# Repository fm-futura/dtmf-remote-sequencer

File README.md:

# Remote power sequencer

This is a very simple device to power on or off the transmitter from our
studio using DTMF tones.

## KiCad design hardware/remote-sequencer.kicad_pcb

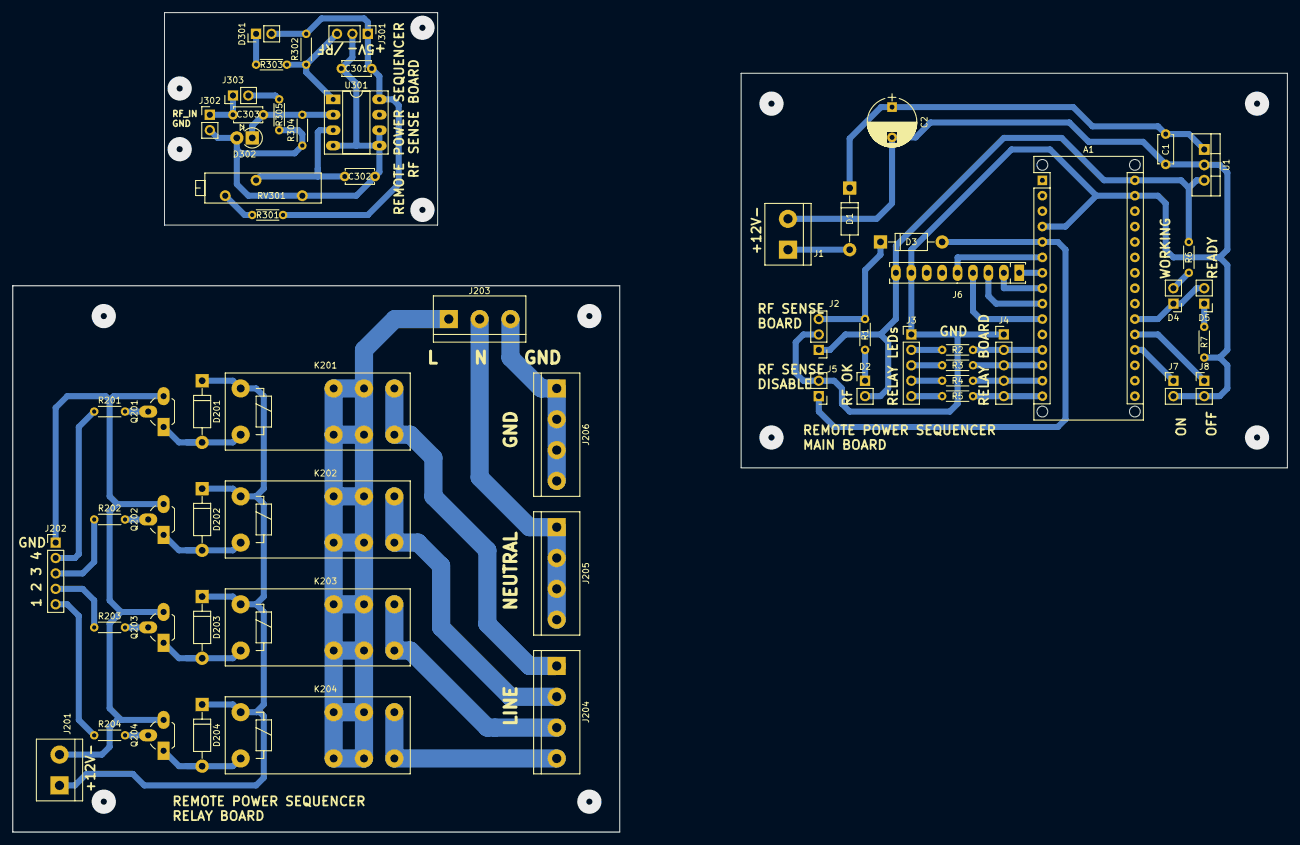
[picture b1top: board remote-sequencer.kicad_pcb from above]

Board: 2 copper layers, 210.0 x 135.0 mm, 61 parts (0 on the bottom side), 51 nets.

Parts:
A1: Arduino_Nano_v3.x; Arduino_Nano_WithMountingHoles
C1, C301, C302, C303: 100n; C_Disc_D4.7mm_W2.5mm_P5.00mm
C2: 2200uF; CP_Radial_D8.0mm_P5.00mm
D1: 1N4007; D_DO-41_SOD81_P10.16mm_Horizontal
D2, D301: RF OK; Socket_Strip_Straight_1x02_Pitch2.54mm
D3, D201, D202, D203, D204: 1N4148; D_DO-41_SOD81_P10.16mm_Horizontal
D4: WORKING; Socket_Strip_Straight_1x02_Pitch2.54mm
D5: READY; Socket_Strip_Straight_1x02_Pitch2.54mm
D302: 1N4148; D_DO-41_SOD81_P2.54mm_Vertical_AnodeUp
J1, J201: PWR_IN; TerminalBlock_bornier-2_P5.08mm
J2, J301: RF_SENSE_BOARD; Pin_Header_Straight_1x03_Pitch2.54mm
J3: RELAY_LED_OUT; Socket_Strip_Straight_1x05_Pitch2.54mm
J4: RELAY_OUT; Socket_Strip_Straight_1x05_Pitch2.54mm
J5: RF_SENSE_DISABLE; Socket_Strip_Straight_1x02_Pitch2.54mm
J6: DTMF_MODULE; SIP9_Housing_BigPads
J7: ON; Socket_Strip_Straight_1x02_Pitch2.54mm
J8: OFF; Socket_Strip_Straight_1x02_Pitch2.54mm
J202: RELAY_IN; Socket_Strip_Straight_1x05_Pitch2.54mm
J203: AC_POWER_IN; TerminalBlock_bornier-3_P5.08mm
J204: PWR_OUT; TerminalBlock_bornier-4_P5.08mm
J205: NEUTRAL_OUT; TerminalBlock_bornier-4_P5.08mm
J206: EARTH_OUT; TerminalBlock_bornier-4_P5.08mm
J302: RF_PROBE_IN; Socket_Strip_Straight_1x02_Pitch2.54mm
J303: 51_ENABLE; Socket_Strip_Straight_1x02_Pitch2.54mm
K201, K202, K203, K204: RELAY_DPDT; Relay_SPDT_Schrack-RP-II-1-16A-FormC_RM5mm
Q201, Q202, Q203, Q204: BC548; TO-92_Rugged
R1, R2, R3, R4, R5, R6, R7, R201, R202, R203, R204, R302, R303: 1k; R_Axial_DIN0204_L3.6mm_D1.6mm_P5.08mm_Horizontal
R301: 10k; R_Axial_DIN0204_L3.6mm_D1.6mm_P5.08mm_Horizontal
R304: 100K; R_Axial_DIN0204_L3.6mm_D1.6mm_P5.08mm_Horizontal
R305: 51; R_Axial_DIN0204_L3.6mm_D1.6mm_P5.08mm_Horizontal
RV301: 1k; Potentiometer_Trimmer_Bourns_3006P
U1: LM7805_TO220; TO-220-3_Vertical
U301: LM393; DIP-8_W7.62mm_Socket_LongPads

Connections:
+5V: A1.30, C301.1, D2.2, D301.2, J2.1, J6.9, J301.1, R6.2, R301.2, R302.2, U1.3, U301.8
+12V: D1.2, D201.1, D202.1, D203.1, D204.1, J1.1, J201.1, K201.A1, K202.A1, K203.A1, K204.A1
/RelayBoard/CTRL_1: J202.2, R201.1
/RelayBoard/CTRL_2: J202.3, R202.1
/RelayBoard/CTRL_3: J202.4, R203.1
/RelayBoard/CTRL_4: J202.5, R204.1
/RelayBoard/PWR_OUT_1: J204.1, K201.14
/RelayBoard/PWR_OUT_2: J204.2, K202.14
/RelayBoard/PWR_OUT_3: J204.3, K203.14
/RelayBoard/PWR_OUT_4: J204.4, K204.14
Earth_Protective: J203.3, J206.1, J206.2, J206.3, J206.4
GND: A1.4, A1.29, C1.2, C2.2, C301.2, C302.2, D302.2, J1.2, J2.2, J3.1, J4.1, J5.2, J6.8, J7.2, J8.2, J201.2, J202.1, J301.2, J302.2, Q201.3, Q202.3, Q203.3, Q204.3, R7.2, R304.1, R305.1, RV301.1, U1.2, U301.4, U301.5, U301.6
LINE: J203.1, K201.11, K201.12, K202.11, K202.12, K203.11, K203.12, K204.11, K204.12
NEUT: J203.2, J205.1, J205.2, J205.3, J205.4
unnamed: A1.5, D3.2, J5.1
unnamed: A1.6, J6.5
unnamed: A1.7, J6.1
unnamed: A1.8, J6.2
unnamed: A1.9, J6.3
unnamed: A1.10, J6.4
unnamed: A1.12, J4.2, R2.1
unnamed: A1.13, J4.3, R3.1
unnamed: A1.14, J4.4, R4.1
unnamed: A1.15, J4.5, R5.1
unnamed: A1.19, J7.1
unnamed: A1.20, J8.1
unnamed: A1.21, D4.1, D5.2
unnamed: C1.1, C2.1, D1.1, U1.1
unnamed: C302.1, RV301.2, U301.3
unnamed: C303.1, D302.1, R304.2, U301.2
unnamed: C303.2, J302.1, J303.1
unnamed: D2.1, R1.2
unnamed: D3.1, J2.3, R1.1
unnamed: D4.2, R6.1
unnamed: D5.1, R7.1
unnamed: D201.2, K201.A2, Q201.1
unnamed: D202.2, K202.A2, Q202.1
unnamed: D203.2, K203.A2, Q203.1
unnamed: D204.2, K204.A2, Q204.1
unnamed: D301.1, R303.2
unnamed: J3.2, R2.2
unnamed: J3.3, R3.2
unnamed: J3.4, R4.2
unnamed: J3.5, R5.2
unnamed: J301.3, R302.1, R303.1, U301.1
unnamed: J303.2, R305.2
unnamed: Q201.2, R201.2
unnamed: Q202.2, R202.2
unnamed: Q203.2, R203.2
unnamed: Q204.2, R204.2
unnamed: R301.1, RV301.3

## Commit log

2018-04-20 Adds basic PlatformIO structure
2018-04-20 Adds initial firmware implementation
2018-12-18 fix overflow when comparing times
2018-12-18 handle rf loss
2018-12-18 fix type overflow
2018-12-18 increase power ok delay
2018-12-18 adds on/off panel inputs
2018-12-19 cleanup: remove unused irq handler
2018-12-19 limit the amount of auto resets
2018-12-19 do nothing if the requested power state matches current state
2018-12-19 adds current state output
2018-12-22 move state output to A2, makes routing easier
2018-12-22 adds main board design files
2018-12-22 adds relay board schematic and pcb
2018-12-27 adds rf sense board schematic and pcb
2018-12-27 update output preferences
2019-01-13 enable interrupt after power on sequence
    There was a very small chance of having an interrupt firing while we
    were powering on and state was set to IDLE (erroneously)
2019-01-13 factor out state led updating, set on first power up
2019-01-13 adds schematics and boards as svg files
